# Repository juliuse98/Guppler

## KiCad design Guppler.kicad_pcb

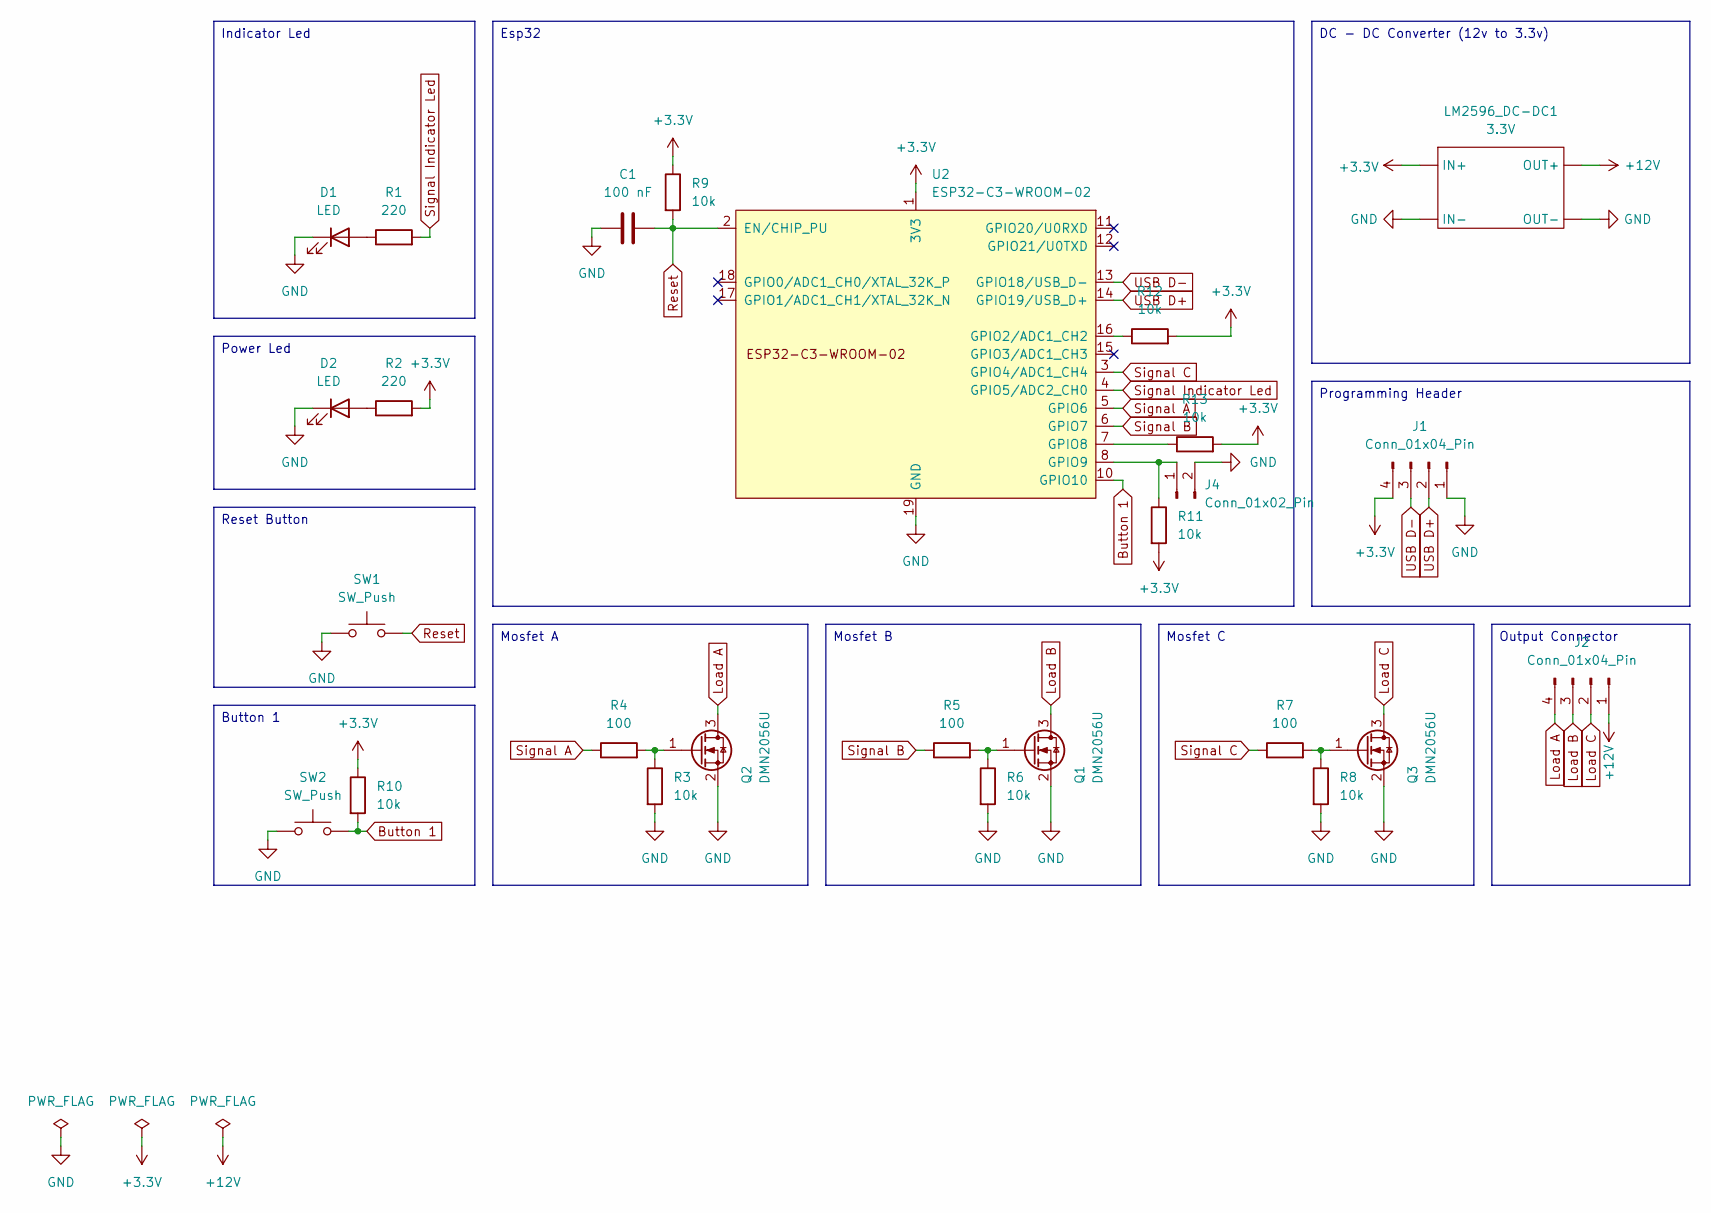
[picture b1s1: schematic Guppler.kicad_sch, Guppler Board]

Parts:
C1: 100 nF; C_0805_2012Metric_Pad1.18x1.45mm_HandSolder
D1, D2: LED; LED_0805_2012Metric_Pad1.15x1.40mm_HandSolder
J1, J2: Conn_01x04_Pin; PinHeader_1x04_P2.54mm_Vertical
J4: Conn_01x02_Pin; PinHeader_1x02_P2.54mm_Vertical
LM2596_DC-DC1: 3.3V; LM2596_DC-DC
Q1, Q2, Q3: DMN2056U; SOT-23
R1, R2: 220; R_0805_2012Metric_Pad1.20x1.40mm_HandSolder
R3, R6, R8, R9, R10, R11, R12, R13: 10k; R_0805_2012Metric_Pad1.20x1.40mm_HandSolder
R4, R5, R7: 100; R_0805_2012Metric_Pad1.20x1.40mm_HandSolder
SW1, SW2: SW_Push; SW_PUSH_6mm_H5mm
U2: ESP32-C3-WROOM-02

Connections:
+3.3V: J1.4, LM2596_DC-DC1.0 (IN+), R2.2, R9.1, R10.1, R11.2, R12.2, R13.2, U2.1 (3V3)
+12V: J2.1, LM2596_DC-DC1.1 (OUT+)
Button 1: R10.2, SW2.2, U2.10 (GPIO10)
GND: C1.1, D1.1 (K), D2.1 (K), J1.1, J4.2, LM2596_DC-DC1.2 (OUT-), LM2596_DC-DC1.3 (IN-), Q1.2 (S), Q2.2 (S), Q3.2 (S), R3.2, R6.2, R8.2, SW1.1, SW2.1, U2.9 (GND), U2.19 (GND)
Load A: J2.4, Q2.3 (D)
Load B: J2.3, Q1.3 (D)
Load C: J2.2, Q3.3 (D)
unnamed: D1.2 (A), R1.1
unnamed: D2.2 (A), R2.1
unnamed: J4.1, R11.1, U2.8 (GPIO9)
unnamed: Q1.1 (G), R5.2, R6.1
unnamed: Q2.1 (G), R3.1, R4.2
unnamed: Q3.1 (G), R7.2, R8.1
unnamed: R12.1, U2.16 (GPIO2/ADC1_CH2)
unnamed: R13.1, U2.7 (GPIO8)
Reset: C1.2, R9.2, SW1.2, U2.2 (EN/CHIP_PU)
Signal A: R4.1, U2.5 (GPIO6)
Signal B: R5.1, U2.6 (GPIO7)
Signal C: R7.1, U2.3 (GPIO4/ADC1_CH4)
Signal Indicator Led: R1.2, U2.4 (GPIO5/ADC2_CH0)
USB D+: J1.2, U2.14 (GPIO19/USB_D+)
USB D-: J1.3, U2.13 (GPIO18/USB_D-)

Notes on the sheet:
Button 1
Output Connector
Indicator Led
Programming Header
Mosfet A
DC - DC Converter (12v to 3.3v)
Power Led
Mosfet C
Mosfet B
Reset Button
Esp32

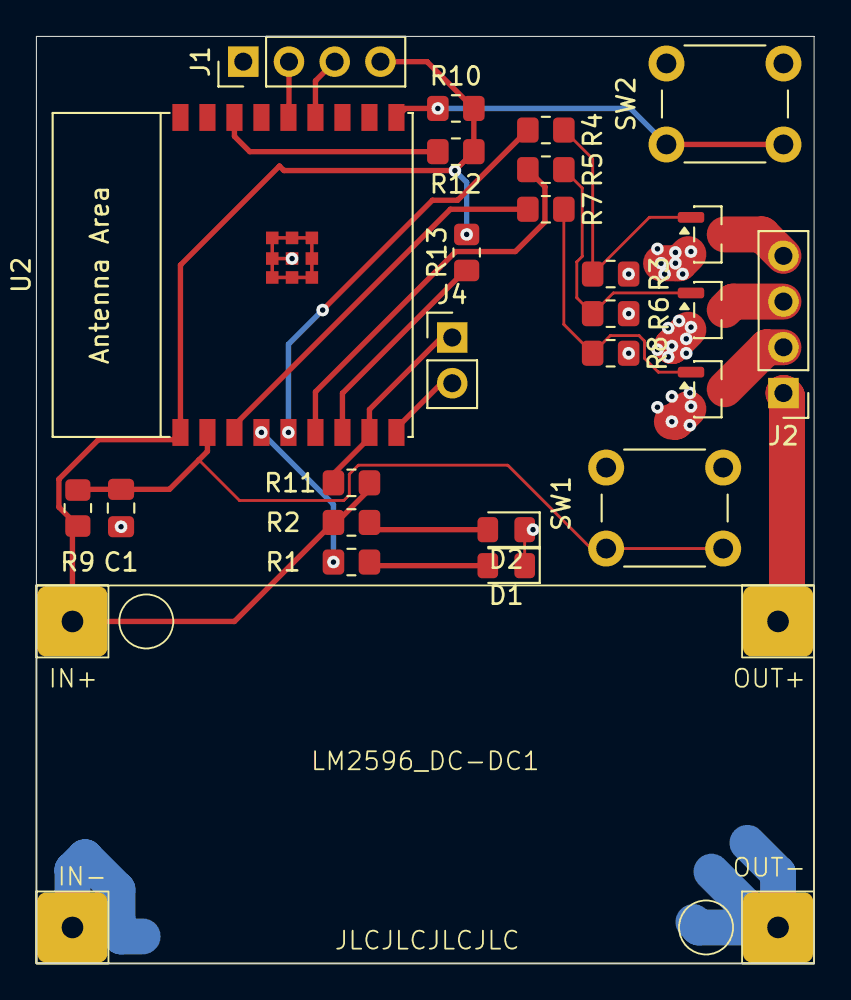
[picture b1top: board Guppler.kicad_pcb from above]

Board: 2 copper layers, 43.2 x 51.5 mm, 26 parts (0 on the bottom side), 22 nets.

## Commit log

2026-02-04 Add basic IO
2026-02-05 Add DC-DC Converter
